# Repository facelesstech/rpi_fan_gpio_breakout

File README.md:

# rpi_fan_gpio_breakout
rpi_fan_gpio_breakout

Blog post - https://facelesstech.wordpress.com/2019/07/20/raspberry-pi-4-fan-and-gpio-breakout-board/
Youtube - https://youtu.be/uS-g6tYt_bE

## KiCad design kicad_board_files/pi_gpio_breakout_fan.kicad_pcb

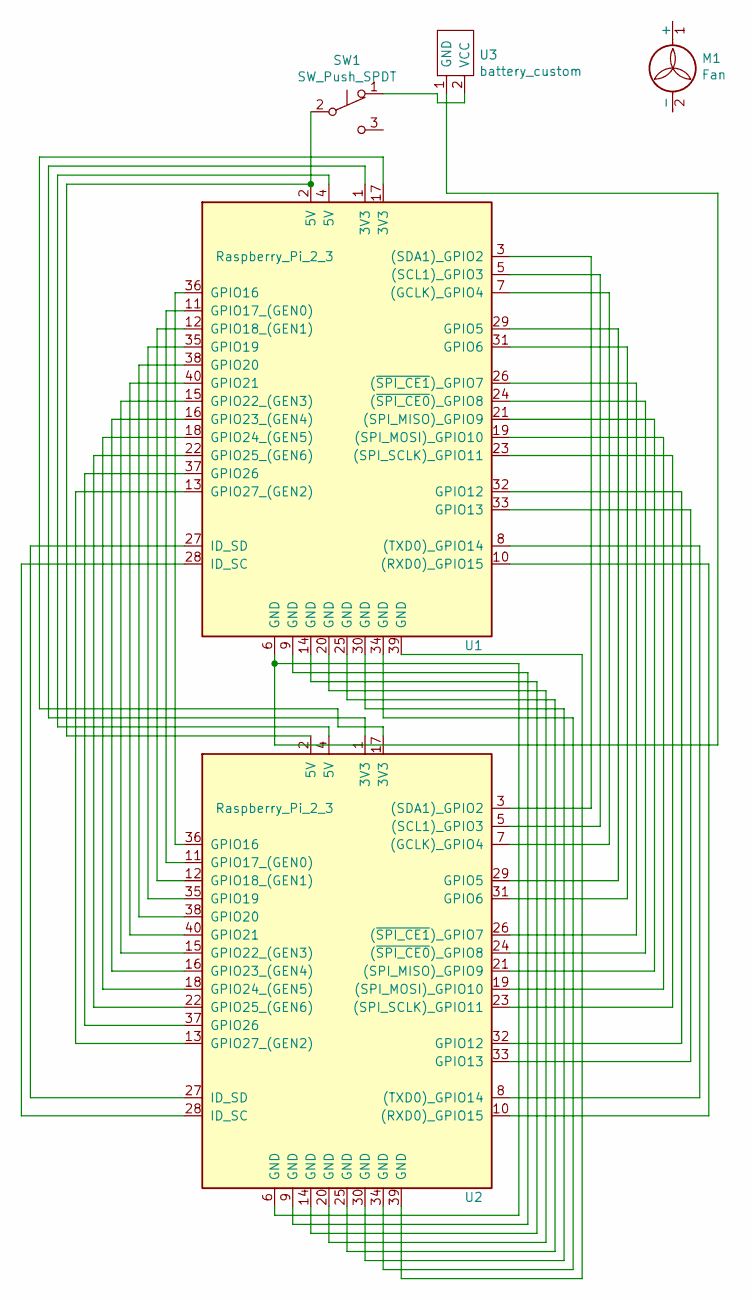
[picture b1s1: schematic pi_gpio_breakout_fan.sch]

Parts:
M1: Fan; 40mm_fan_2_wire
SW1: SW_Push_SPDT; 3_pin_switch__right_angle_custom
U1, U2: Raspberry_Pi_2_3; Pin_Header_Straight_2x20
U3: battery_custom; jst_2pin_right_angle

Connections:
unnamed: SW1.1 (A), U3.2 (VCC)
unnamed: SW1.2 (B), U1.2 (5V), U2.2 (5V)
unnamed: U1.1 (3V3), U2.1 (3V3)
unnamed: U1.3 ((SDA1)_GPIO2), U2.3 ((SDA1)_GPIO2)
unnamed: U1.4 (5V), U2.4 (5V)
unnamed: U1.5 ((SCL1)_GPIO3), U2.5 ((SCL1)_GPIO3)
unnamed: U1.6 (GND), U2.6 (GND), U3.1 (GND)
unnamed: U1.7 ((GCLK)_GPIO4), U2.7 ((GCLK)_GPIO4)
unnamed: U1.8 ((TXD0)_GPIO14), U2.8 ((TXD0)_GPIO14)
unnamed: U1.9 (GND), U2.9 (GND)
unnamed: U1.10 ((RXD0)_GPIO15), U2.10 ((RXD0)_GPIO15)
unnamed: U1.11 (GPIO17_(GEN0)), U2.11 (GPIO17_(GEN0))
unnamed: U1.12 (GPIO18_(GEN1)), U2.12 (GPIO18_(GEN1))
unnamed: U1.13 (GPIO27_(GEN2)), U2.13 (GPIO27_(GEN2))
unnamed: U1.14 (GND), U2.14 (GND)
unnamed: U1.15 (GPIO22_(GEN3)), U2.15 (GPIO22_(GEN3))
unnamed: U1.16 (GPIO23_(GEN4)), U2.16 (GPIO23_(GEN4))
unnamed: U1.17 (3V3), U2.17 (3V3)
unnamed: U1.18 (GPIO24_(GEN5)), U2.18 (GPIO24_(GEN5))
unnamed: U1.19 ((SPI_MOSI)_GPIO10), U2.19 ((SPI_MOSI)_GPIO10)
unnamed: U1.20 (GND), U2.20 (GND)
unnamed: U1.21 ((SPI_MISO)_GPIO9), U2.21 ((SPI_MISO)_GPIO9)
unnamed: U1.22 (GPIO25_(GEN6)), U2.22 (GPIO25_(GEN6))
unnamed: U1.23 ((SPI_SCLK)_GPIO11), U2.23 ((SPI_SCLK)_GPIO11)
unnamed: U1.24 ((~SPI_CE0~)_GPIO8), U2.24 ((~SPI_CE0~)_GPIO8)
unnamed: U1.25 (GND), U2.25 (GND)
unnamed: U1.26 ((~SPI_CE1~)_GPIO7), U2.26 ((~SPI_CE1~)_GPIO7)
unnamed: U1.27 (ID_SD), U2.27 (ID_SD)
unnamed: U1.28 (ID_SC), U2.28 (ID_SC)
unnamed: U1.29 (GPIO5), U2.29 (GPIO5)
unnamed: U1.30 (GND), U2.30 (GND)
unnamed: U1.31 (GPIO6), U2.31 (GPIO6)
unnamed: U1.32 (GPIO12), U2.32 (GPIO12)
unnamed: U1.33 (GPIO13), U2.33 (GPIO13)
unnamed: U1.34 (GND), U2.34 (GND)
unnamed: U1.35 (GPIO19), U2.35 (GPIO19)
unnamed: U1.36 (GPIO16), U2.36 (GPIO16)
unnamed: U1.37 (GPIO26), U2.37 (GPIO26)
unnamed: U1.38 (GPIO20), U2.38 (GPIO20)
unnamed: U1.39 (GND), U2.39 (GND)
unnamed: U1.40 (GPIO21), U2.40 (GPIO21)

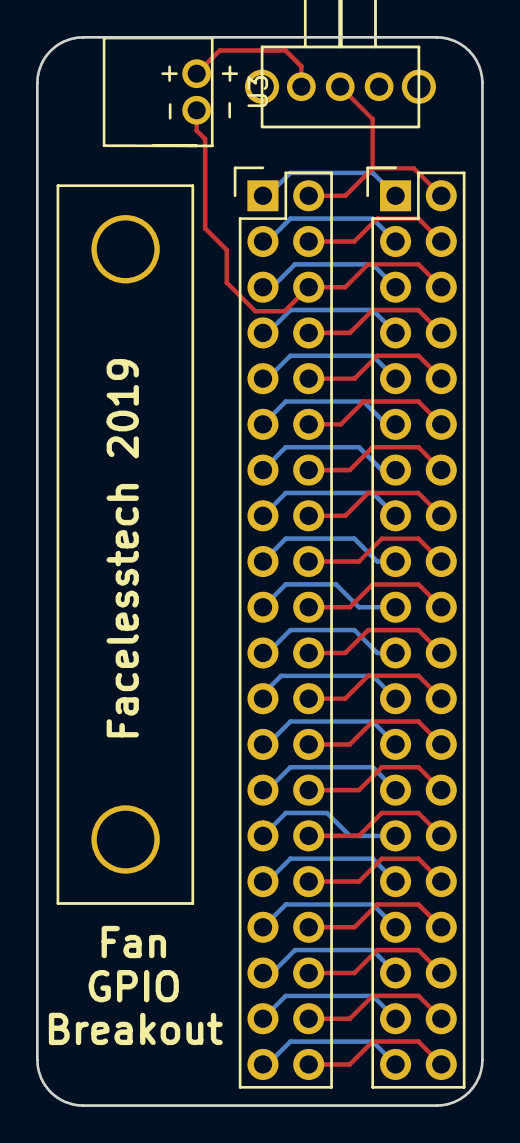
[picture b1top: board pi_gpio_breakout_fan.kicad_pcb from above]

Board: 2 copper layers, 24.7 x 59.3 mm, 5 parts (0 on the bottom side), 41 nets.

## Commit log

2019-07-06 kicad board files
2020-02-27 added links to readme
